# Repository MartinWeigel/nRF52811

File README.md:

# nRF52811 PCB

This is the schematics and footprint of a basic board with the [nRF52811 microcontroller](https://www.nordicsemi.com/?sc_itemid=%7B7CBDF55C-9745-4A7D-A491-5B66AE9454B6%7D
) from [Nordic Semiconductor](https://devzone.nordicsemi.com). This microcontroller supports Bluetooth Low Energy 5.1. The board contains one LED and can be powered either over Micro-USB or a Li-Po battery. It requires a SWD-capable programmer for programming and debugging.

The board was primarily designed for testing and familiarizing myself with [KiCad 5.1](http://www.kicad.org).

## Design

## License
<br />This work is licensed under a <a rel="license" href="http://creativecommons.org/licenses/by/4.0/">Creative Commons Attribution 4.0 International License</a>.

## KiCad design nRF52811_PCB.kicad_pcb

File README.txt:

# nRF52811 PCB

This is the schematics and footprint of a basic board with the [nRF52811 microcontroller](https://www.nordicsemi.com/?sc_itemid=%7B7CBDF55C-9745-4A7D-A491-5B66AE9454B6%7D
) from [Nordic Semiconductor](https://devzone.nordicsemi.com). This microcontroller supports Bluetooth Low Energy 5.1. The board contains one LED and can be powered either over Micro-USB or a Li-Po battery. It requires a SWD-capable programmer for programming and debugging.

The board was primarily designed for testing and familiarizing myself with [KiCad 5.1](http://www.kicad-pcb.org).

## Design

## License
<br />This work is licensed under a <a rel="license" href="http://creativecommons.org/licenses/by/4.0/">Creative Commons Attribution 4.0 International License</a>.

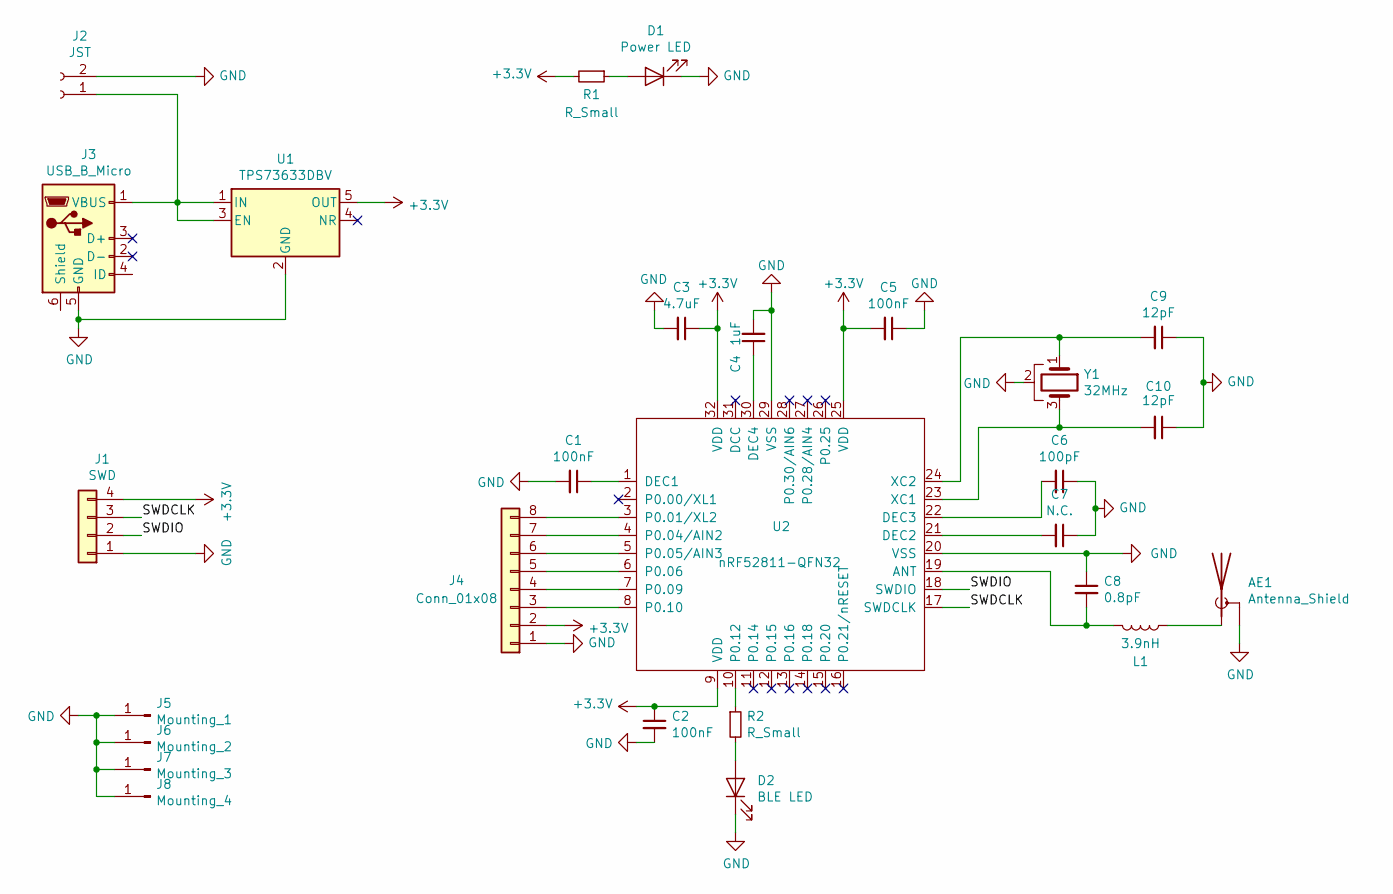
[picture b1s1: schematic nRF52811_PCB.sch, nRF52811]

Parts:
AE1: Antenna_Shield; Texas_SWRA117D_2.4GHz_Left
C1, C2, C5: 100nF; C_0805_2012Metric_Pad1.15x1.40mm_HandSolder
C3: 4.7uF; C_0805_2012Metric_Pad1.15x1.40mm_HandSolder
C4: 1uF; C_0805_2012Metric_Pad1.15x1.40mm_HandSolder
C6: 100pF; C_0805_2012Metric_Pad1.15x1.40mm_HandSolder
C7: N.C.; C_0805_2012Metric_Pad1.15x1.40mm_HandSolder
C8: 0.8pF; C_0805_2012Metric_Pad1.15x1.40mm_HandSolder
C9, C10: 12pF; C_0805_2012Metric_Pad1.15x1.40mm_HandSolder
D1: Power LED; LED_0805_2012Metric_Pad1.15x1.40mm_HandSolder
D2: BLE LED; LED_0805_2012Metric_Pad1.15x1.40mm_HandSolder
J1: SWD; PinHeader_1x04_P2.54mm_Vertical
J2: JST; JST_EH_S2B-EH_1x02_P2.50mm_Horizontal
J3: USB_B_Micro; USB_Micro-B_Amphenol_10103594-0001LF_Horizontal
J4: Conn_01x08; PinSocket_1x08_P2.54mm_Vertical
J5: Mounting_1; MountingHole_2.2mm_M2_DIN965_Pad
J6: Mounting_2; MountingHole_2.2mm_M2_DIN965_Pad
J7: Mounting_3; MountingHole_2.2mm_M2_DIN965_Pad
J8: Mounting_4; MountingHole_2.2mm_M2_DIN965_Pad
L1: 3.9nH; L_0805_2012Metric_Pad1.15x1.40mm_HandSolder
R1, R2: R_Small; R_0805_2012Metric_Pad1.15x1.40mm_HandSolder
U1: TPS73633DBV; SOT-23-5_HandSoldering
U2: nRF52811-QFN32; LQFP-32_5x5mm_P0.5mm
Y1: 32MHz; Crystal_SMD_3225-4Pin_3.2x2.5mm_HandSoldering

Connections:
+3V3: C2.1, C3.1, C5.2, J1.4, J4.2, R1.2, U1.5 (OUT), U2.9 (VDD), U2.25 (VDD), U2.32 (VDD)
/SWDCLK: J1.3, U2.17 (SWDCLK)
/SWDIO: J1.2, U2.18 (SWDIO)
GND: AE1.2 (Shield), C1.2, C2.2, C3.2, C4.2, C5.1, C6.1, C7.1, C8.1, C9.1, C10.1, D1.1 (K), D2.1 (K), J1.1, J2.2, J3.5 (GND), J4.1, J5.1, J6.1, J7.1, J8.1, U1.2 (GND), U2.20 (VSS), U2.29 (VSS), Y1.2
unnamed: AE1.1 (A), L1.1
unnamed: C1.1, U2.1 (DEC1)
unnamed: C4.1, U2.30 (DEC4)
unnamed: C6.2, U2.22 (DEC3)
unnamed: C7.2, U2.21 (DEC2)
unnamed: C8.2, L1.2, U2.19 (ANT)
unnamed: C9.2, U2.24 (XC2), Y1.1
unnamed: C10.2, U2.23 (XC1), Y1.3
unnamed: D1.2 (A), R1.1
unnamed: D2.2 (A), R2.2
unnamed: J2.1, J3.1 (VBUS), U1.1 (IN), U1.3 (EN)
unnamed: J4.3, U2.8 (P0.10)
unnamed: J4.4, U2.7 (P0.09)
unnamed: J4.5, U2.6 (P0.06)
unnamed: J4.6, U2.5 (P0.05/AIN3)
unnamed: J4.7, U2.4 (P0.04/AIN2)
unnamed: J4.8, U2.3 (P0.01/XL2)
unnamed: R2.1, U2.10 (P0.12)

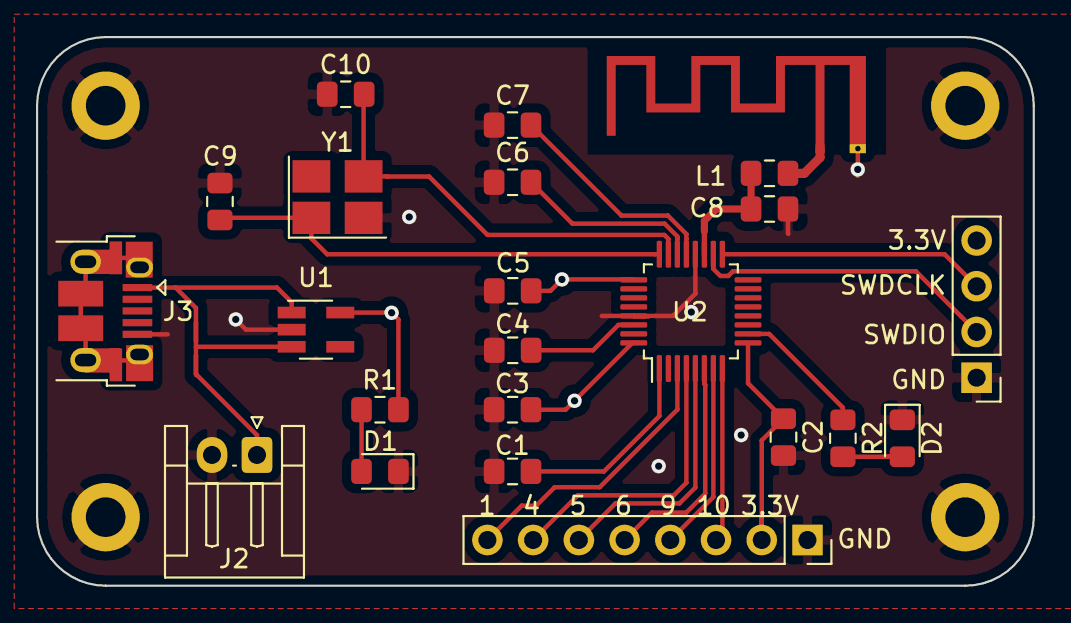
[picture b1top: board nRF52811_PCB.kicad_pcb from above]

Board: 4 copper layers, 55.4 x 30.5 mm, 27 parts (0 on the bottom side), 22 nets.

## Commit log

2019-10-24 Version 1
2019-10-24 Changed README extension
2019-11-13 Added all pin names in nRF52811 library
2019-11-13 Added 3D components to rendering
2021-11-10 Update README.md
    https://forum.kicad.info/t/warning-avoid-all-links-to-kicad-pcb-org-use-kicad-org/31521

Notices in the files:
nRF52811_PCB.kicad_pcb:
License: CC BY 4.0
nRF52811_PCB.sch:
https://creativecommons.org/licenses/by/4.0
